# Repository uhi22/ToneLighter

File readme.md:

# ToneLighter

LED stripe controlled by music

## Features

- LED stripe with WS2812 RGB LEDs
- Microphone to catch the music
- Arduino Pro mini which evaluates the audio level and controls the LED stripe
- Second Arduino Pro mini which has a 433 MHz receiver connected, to receive remote control commands
- Serial communication from the one to the other Arduino
- Powered by 3.7V LiIon accus

## Bug List

### Bugs in v2023-05-22 Layout

- R9 value is not printed on PCB (1M)
- R6 value is not printed on PCB (47k)
- C4 value is not printed on PCB and schematic (100n? or bigger?)
- Arduino debug connector is swapped (maybe there are different variants out there???)

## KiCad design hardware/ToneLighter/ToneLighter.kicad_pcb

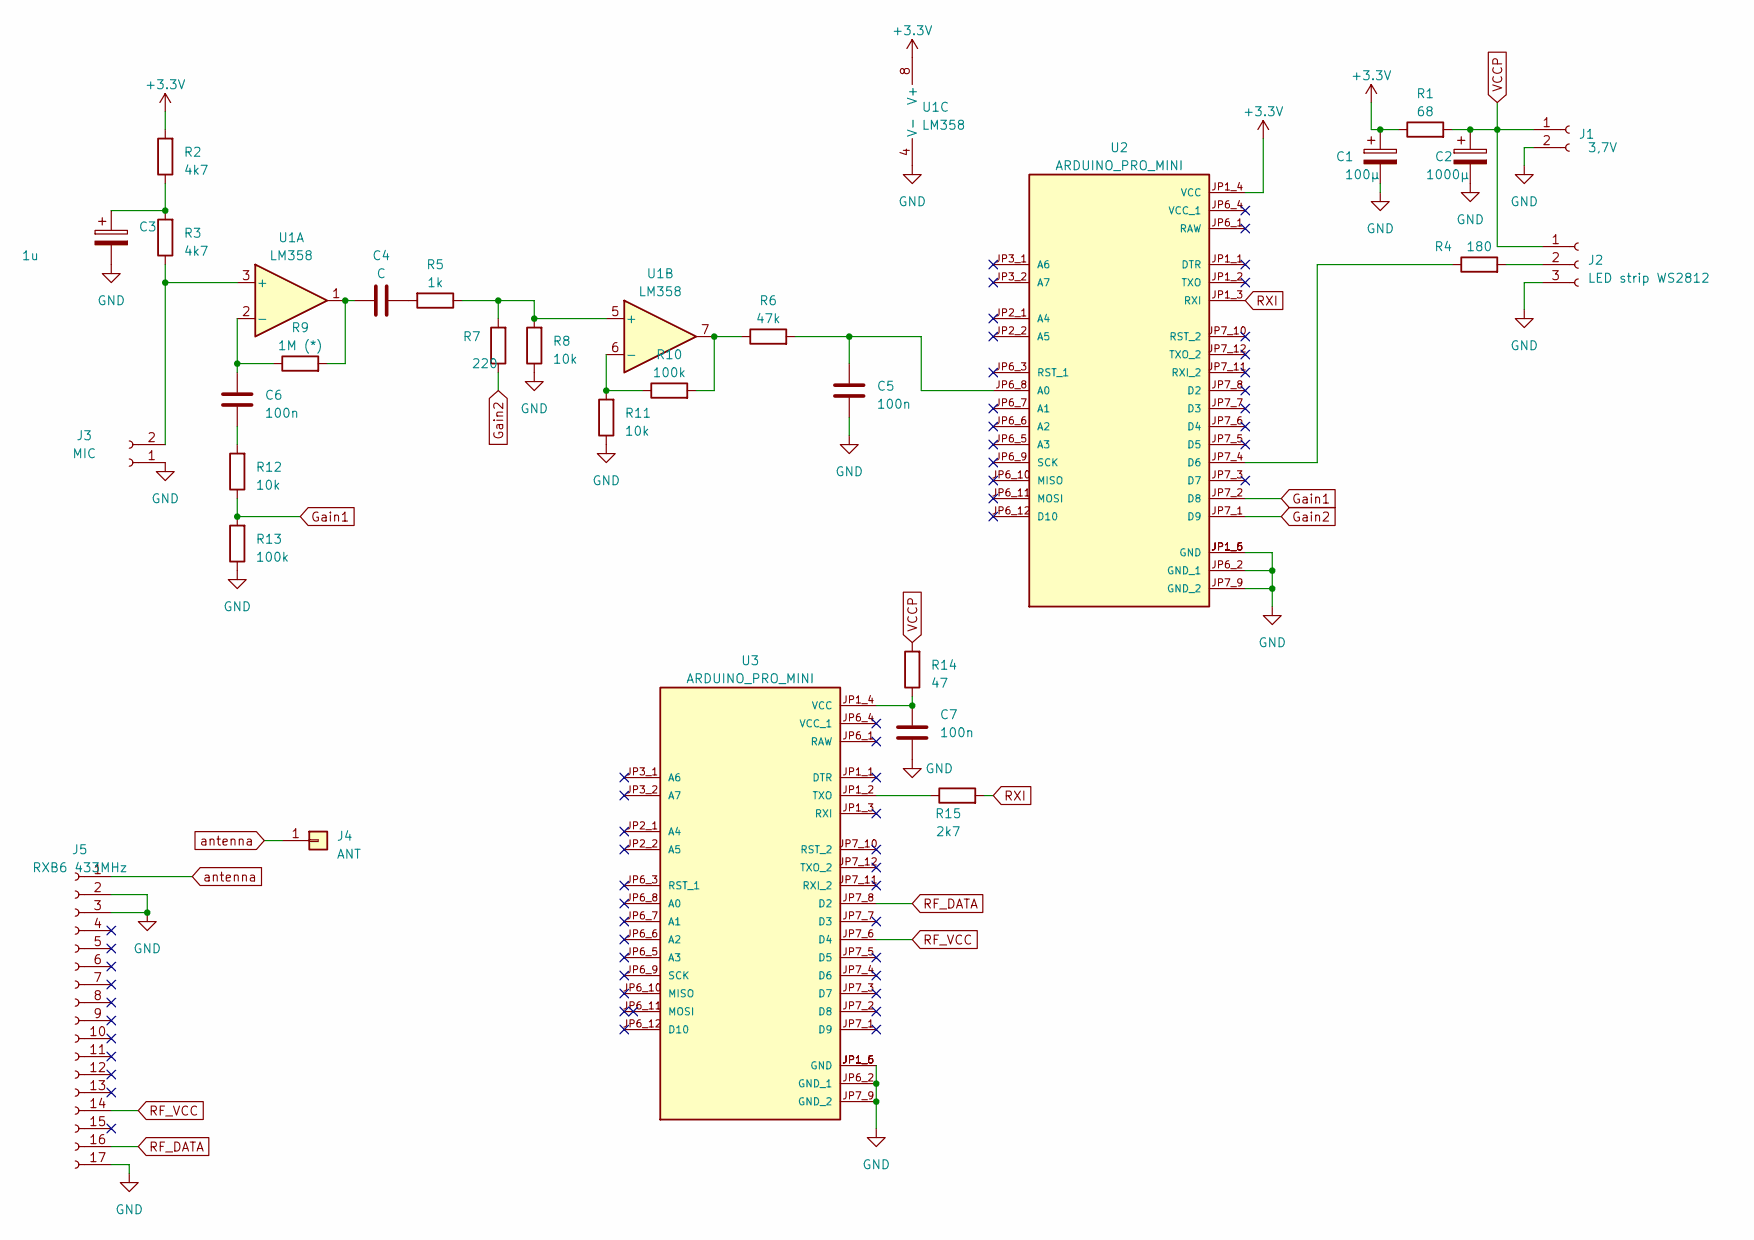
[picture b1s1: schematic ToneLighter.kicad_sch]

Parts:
C1: 100µ; CP_Radial_D5.0mm_P2.50mm
C2: 1000µ; CP_Radial_D5.0mm_P2.50mm
C3: 1u; CP_Radial_D5.0mm_P2.50mm
C4: C; C_1206_3216Metric
C5, C6, C7: 100n; C_1206_3216Metric
J1: 3,7V; PinHeader_1x02_P2.54mm_Vertical
J2: LED strip WS2812; PinHeader_1x03_P2.54mm_Vertical
J3: MIC; PinHeader_1x02_P2.54mm_Vertical
J4: ANT; Pin_D0.7mm_L6.5mm_W1.8mm_FlatFork
J5: RXB6 433MHz; PinHeader_1x17_P2.54mm_Vertical
R1: 68; R_1206_3216Metric_Pad1.30x1.75mm_HandSolder
R2, R3: 4k7; R_1206_3216Metric_Pad1.30x1.75mm_HandSolder
R4: 180; R_1206_3216Metric_Pad1.30x1.75mm_HandSolder
R5: 1k; R_1206_3216Metric_Pad1.30x1.75mm_HandSolder
R6: 47k; R_1206_3216Metric_Pad1.30x1.75mm_HandSolder
R7: 220; R_1206_3216Metric_Pad1.30x1.75mm_HandSolder
R8, R11, R12: 10k; R_1206_3216Metric_Pad1.30x1.75mm_HandSolder
R9: 1M (*); R_1206_3216Metric_Pad1.30x1.75mm_HandSolder
R10, R13: 100k; R_1206_3216Metric_Pad1.30x1.75mm_HandSolder
R14: 47; R_1206_3216Metric_Pad1.30x1.75mm_HandSolder
R15: 2k7; R_1206_3216Metric_Pad1.30x1.75mm_HandSolder
U1: LM358; DIP-8_W7.62mm
U2, U3: ARDUINO_PRO_MINI; MODULE_ARDUINO_PRO_MINI; PARTREV N/A

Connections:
+3.3V: C1.1, R1.1, R2.2, U1.8 (V+), U2.JP1_4 (VCC)
GND: C1.2, C2.2, C3.2, C5.2, C7.2, J1.2, J2.3, J3.1, J5.2, J5.3, J5.17, R8.1, R11.1, R13.1, U1.4 (V-), U2.JP1_5 (GND), U2.JP1_6 (GND), U2.JP6_2 (GND_1), U2.JP7_9 (GND_2), U3.JP1_5 (GND), U3.JP1_6 (GND), U3.JP6_2 (GND_1), U3.JP7_9 (GND_2)
Gain1: R12.1, R13.2, U2.JP7_2 (D8)
Gain2: R7.1, U2.JP7_1 (D9)
unnamed: C3.1, R2.1, R3.2
unnamed: C4.1, R9.2, U1.1
unnamed: C4.2, R5.2
unnamed: C6.2, R12.2
unnamed: J2.2, R4.2
unnamed: J3.2, R3.1, U1.3 (+)
unnamed: R6.1, R10.2, U1.7
unnamed: C6.1, R9.1, U1.2 (-)
unnamed: R5.1, R7.2, R8.2, U1.5 (+)
unnamed: R10.1, R11.2, U1.6 (-)
unnamed: C5.1, R6.2, U2.JP6_8 (A0)
unnamed: R4.1, U2.JP7_4 (D6)
unnamed: R15.1, U3.JP1_2 (TXO)
unnamed: C7.1, R14.1, U3.JP1_4 (VCC)
RF_DATA: J5.16, U3.JP7_8 (D2)
RF_VCC: J5.14, U3.JP7_6 (D4)
RXI: R15.2, U2.JP1_3 (RXI)
VCCP: C2.1, J1.1, J2.1, R1.2, R14.2
antenna: J4.1, J5.1

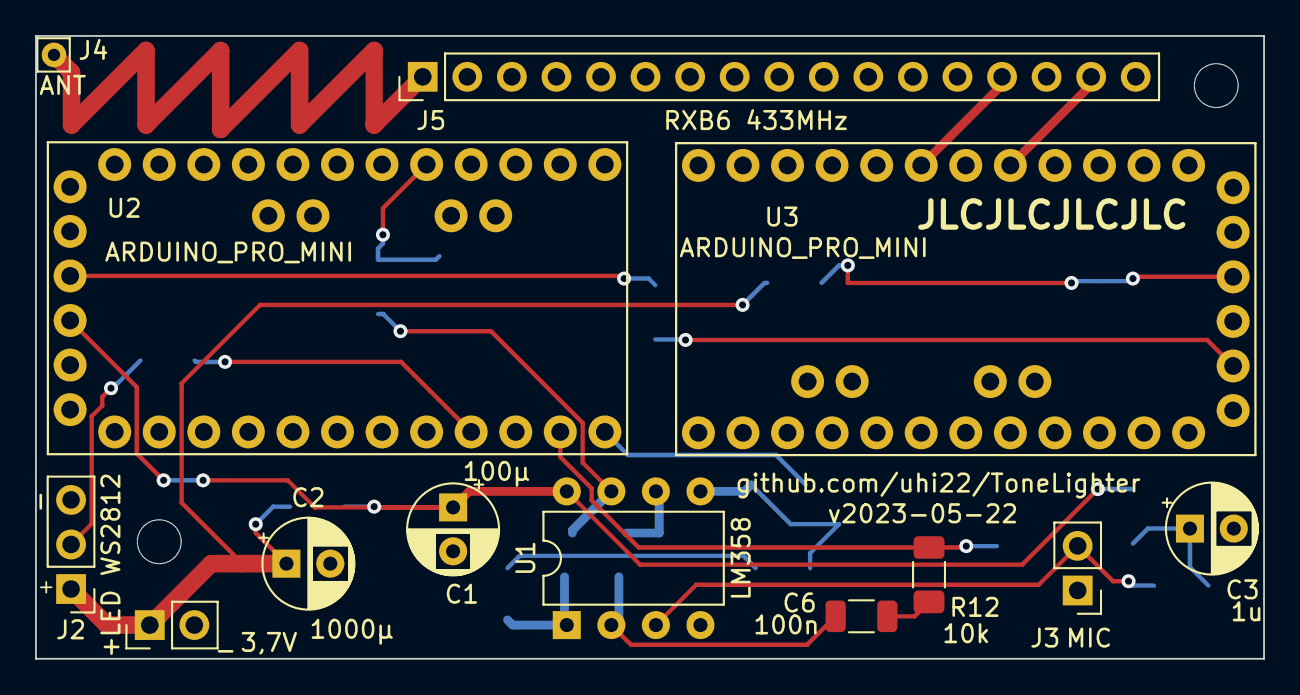
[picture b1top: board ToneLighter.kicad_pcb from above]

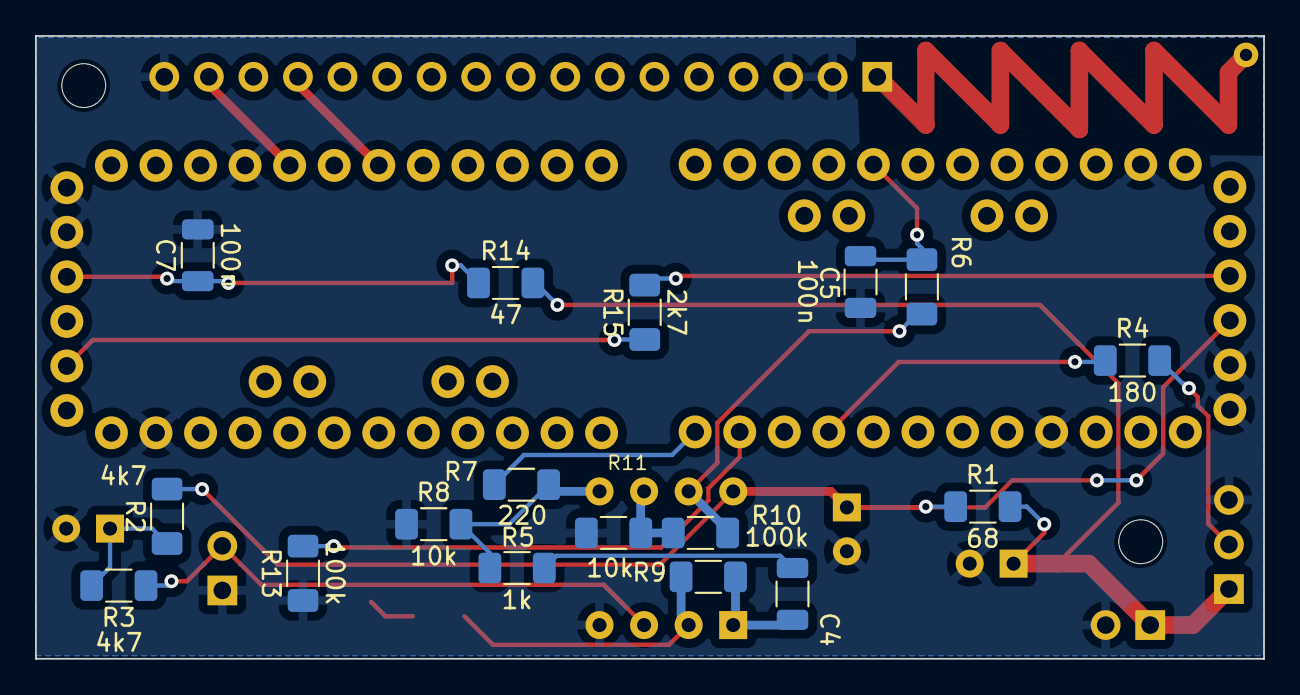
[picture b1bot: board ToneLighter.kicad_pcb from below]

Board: 2 copper layers, 70.0 x 35.5 mm, 30 parts (17 on the bottom side), 23 nets.

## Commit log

2023-05-23 added readme
2023-05-23 added arduino projects
2023-06-17 docu: bugs in pcb. feature: prepared gain outputs
